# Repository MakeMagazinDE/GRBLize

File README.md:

Maker Media GmbH und c't, Heise Zeitschriften Verlag

***

# GRBLize V1.4

### CNC-Steuerung für GRBL-JOG Projekt

Erstellt mit Delphi XE8 Starter. Bitte beachten Sie unbedingt den Artikel in **[c't Hacks 4/2014](http://shop.heise.de/katalog/ct-hacks-4-2014)**. 

**Derzeit gibt es [Delphi 10.1 Berlin Starter](https://www.embarcadero.com/de/products/delphi/starter/promotional-download) kostenlos!** 

Ausführbare Datei (.EXE, Win32) im Verzeichnis 
**[/bin](https://github.com/heise/GRBLize/tree/master/bin)**, benötigt 
"default.job", ggf. die Beispiel-Plot-Dateien und gegebenenfalls ftd2xx.dll, 
letzteres aber nur, falls nicht ohnehin schon im System vom FTDI-Treiber-
Download installiert.

Auf der rechten Spalte der Github-Seite finden Sie den Button "Download ZIP". 
Dies lädt das komplette Projekt herunter einschl. Sourcen. Nach Entpacken findet 
sich das Windows-Executable (32 Bit) im Unterverzeichnis /bin.

Das Projekt befindet sich noch in Entwicklung, bitte auf evt. Updates prüfen. 
Die passende GRBL-Steuerplatine finden Sie in unserem Github-Repo **[GRBL-
JOG](https://github.com/heise/GRBL-JOG)**. Die neueste Version unterstützt jetzt 
auch GRBL 0.9j sowie GRBL auf Arduino und ähnlichen Boards.

### Version History

- 1.5 noGL: Version ohne das recht umständlich zu installierende OpenGL-Derivat "GLscene"
- 1.5: Unterstützung für GRBL 1.1 kompilierbar, noch nicht vollständig getestet. 
Binary ist für GRBL 0.9j. Korrekte Behandlung der File-XY-Offsets auch bei Roatation/Mirror, Pfade im 
Drawing Window einzeln deaktivierbar. Instant-Mill-Funktionen für Kreise und Rechtecke ab Tool-Position.
- 1.4: Stark umgebaute Programmstruktur. CANCEL funktioniert endlich wie es soll. Ausgabe optimiert. ATC getestet. PCB Import stark vereinfacht. 
- 1.1b: Interface for pcb2gcode.exe in Utilities/Tools tab. Revised interpreter for excellon files. Added 2D G-Code and simple SVG import to interface with pcb2gcode.
- 1.0b: Supports serial COM port as well as direct FTDI serial communications. Re-written robust protocol engine. New simulation for G-Codes as a finite elements model in 3 resolutions. Some bugs fixed. Suports GRBL 0.8x and new GRBL 0.9j. New on-screen jog pad for use with other boards than GRBL-JOG. Supports GRBL running on a plain Arduino.
- 0.96d: On run, will keep Z up at park position height until first mill to clear work part. 
- 0.96b: bugfix on FTDI class, new "Z Feed Scaling" parameter, multiplies XY feed value for Z to prevent tool damage (<1 = slower). Also useful with c't woodmill (>1 = faster, otherwise Z feed will be too slow).
- 0.95b: First public beta
- 0.94a: Internal alpha, some serious bugs

### CNC Control Software for GRBL Jogger Project

Executable for Windows XP/7/8 in folder **[/bin](https://github.com/heise/GRBLize/tree/master/bin)**. No Installation required, but configuration file "default.job" and example plot files 
must be placed in same folder. Please see article in **[c't Hacks 4/2014](http://shop.heise.de/katalog/ct-hacks-4-2014)** for usage.

Version in Master branch made with Delphi 2005 PE. Sources to be compiled with Borland Delphi 2005 Personal Edition (and up) for those interested in improving it. GRBLize 
uses ftdiclass component from Michael "Zipplet" Nixon, Clipper library by Angus Johnson and GLscene OpenGL component.

Borland Delphi 2005 Personal Edition was downloadable for free some time ago, also included on some computer magazine CDs/DVDs as on c't 13/2005. It should be still available for free on http://delphi.developpez.com/delphi2005/

Delphi 2005 still works fine on Windows 7 if you add the new string value "$(BDS)\Bin\delphicoreide90.bpl" = "Delphi Core IDE" 
to the "HKEY_CURRENT_USER\Software\Borland\BDS\3.0\Known IDE Packages" registry key. Otherwise you'll get an access 
violation error on rtl90.bpl on exit of IDE. 

On Windows 7 latest update, the DZ Line Editor Fix (http://sourceforge.net/projects/dzeditorlineendsfix/) must be installed.

For Delphi 2005 PE, if you want to compile and install the design-time support for GLScene in folder Delphi2005, you 
will need to:

- rename FAKE_xmlrtl.dcp to xmlrtl.dcp
- copy/move it to your BDS\3.0\lib directory

This will take care of the warning (doesn't add xmlrtl functionality however, the dcp is empty). Source:
http://andy.jgknet.de/oss/kylix/wiki/index.php/Delphi_2005_Personal_Edition_xmlrtl.dcp_fake

Do not hesitate to port the project to [Lazarus](http://www.lazarus.freepascal.org), a free Delphi clone available for Linux and Windows.

Please note: some parts may rely on comma as a decimal separator in tables, please check first.

(c) by Carsten Meyer, Redaktion c't Hacks/Make Deutschland, cm@ct.de, 12/2014.

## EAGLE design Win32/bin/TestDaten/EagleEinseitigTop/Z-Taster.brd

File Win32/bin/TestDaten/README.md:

#GRBLize

###CNC-Steuerung für GRBL-JOG Projekt

Ausführbare Datei für Windows XP/7/8. Benötigt keine Installation, lediglich die Kofigurationsdatei
"default.job" und ggf. die Beispiele im gleichen Verzeichnis. FTDI-Treiber für serielles Interface müssen installiert sein.

Bitte beachten Sie unbedingt den Artikel in **[c't Hacks 4/2014](http://shop.heise.de/katalog/ct-hacks-4-2014)** mit der 
Anleitung für dieses Programm.

###CNC Control Software for GRBL Jogger Project

Executable for Windows XP/7/8. No Installation required, but configuration file "default.job" and example plot files 
must be placed in same folder. Please see article in **[c't Hacks 4/2014](http://shop.heise.de/katalog/ct-hacks-4-2014)** 
(sorry, german only) for usage.

(c) by Carsten Meyer, Redaktion c't Hacks/Make Deutschland, cm@ct.de, 12/2014.

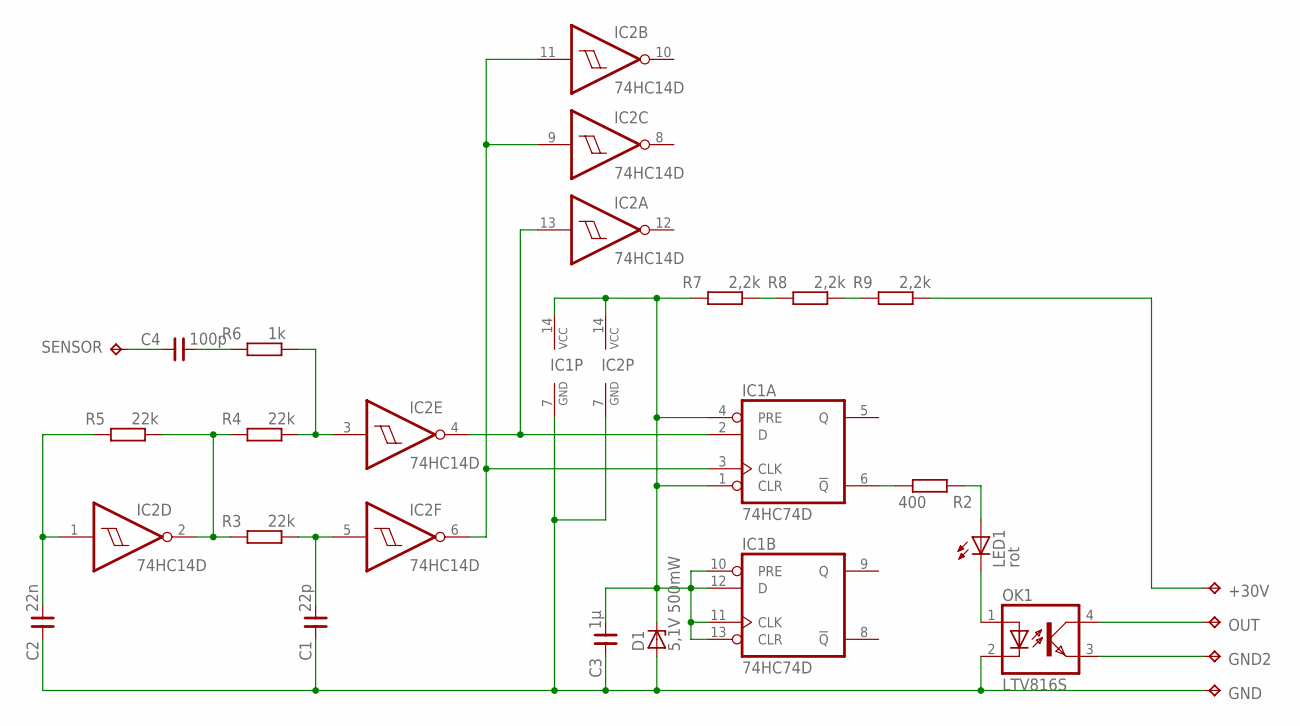
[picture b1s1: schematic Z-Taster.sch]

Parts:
+30V: TPTP20SQ; TP20SQ
C1: 22p; R0805
C2: 22n; R0805
C3: 1µ; R0805
C4: 100p; R0805
D1: 5,1V 500mW; SOD80C
GND, GND2: TPTP18SQ; TP18SQ
IC1: 74HC74D; SO14
IC2: 74HC14D; SO14
LED1: rot; LED0805
OK1: LTV816S; SMD4
OUT: TPTP18SQ; TP18SQ
R2: 400; R0805
R3, R4, R5: 22k; R0805
R6: 1k; R0805
R7, R8, R9: 2,2k; R0805
SENSOR: TPTP18SQ; TP18SQ

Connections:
GND: C1.1, C2.1, C3.1, D1.A, GND.TP, IC1.7 (GND), IC2.7 (GND), OK1.2 (C)
unnamed: C4.2, R6.1
unnamed: IC2.2 (O), R3.1, R4.1, R5.2
unnamed: IC2.3 (I), R4.2, R6.2
unnamed: C2.2, IC2.1 (I), R5.1
unnamed: C1.2, IC2.5 (I), R3.2
unnamed: IC1.2 (D), IC2.4 (O), IC2.13 (I)
unnamed: IC1.3 (CLK), IC2.6 (O), IC2.9 (I), IC2.11 (I)
unnamed: R7.2, R8.1
unnamed: R8.2, R9.1
unnamed: LED1.A, R2.1
unnamed: IC1.6 (!Q), R2.2
unnamed: +30V.TP, R9.2
unnamed: LED1.C, OK1.1 (A)
unnamed: OK1.4 (COL), OUT.TP
unnamed: GND2.TP, OK1.3 (EMIT)
SENSOR: C4.1, SENSOR.TP
VCC: C3.2, D1.C, IC1.1 (CLR), IC1.4 (PRE), IC1.10 (PRE), IC1.11 (CLK), IC1.12 (D), IC1.13 (CLR), IC1.14 (VCC), IC2.14 (VCC), R7.1

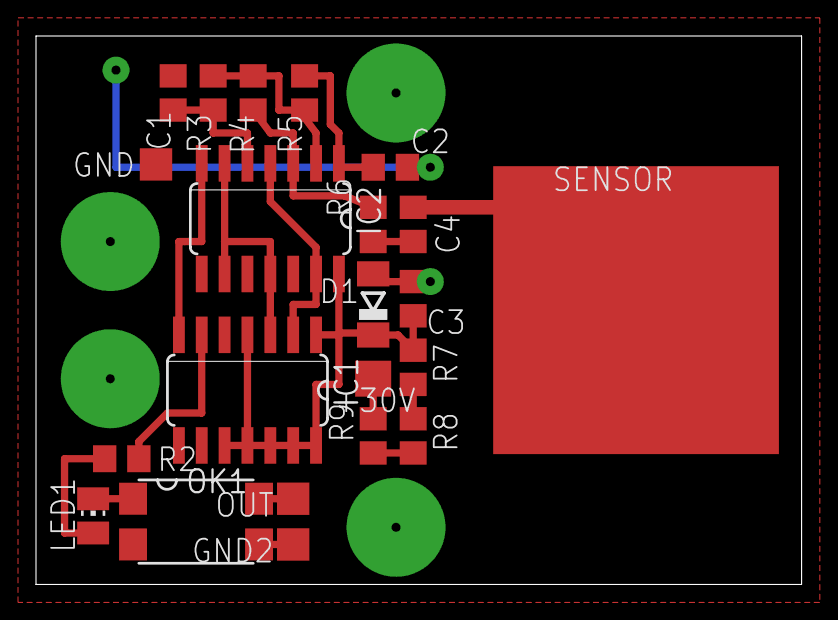
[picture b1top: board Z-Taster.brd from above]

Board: 2 copper layers, 42.5 x 30.5 mm, 22 parts (0 on the bottom side), 18 nets.

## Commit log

2014-12-10 new folder
2014-12-10 new GRBLize
2014-12-10 new test
2014-12-10 GRBLize 0.9
2014-12-10 #0.94
2014-12-10 #0.94b
2014-12-11 #0.95b
2014-12-11 edit
2014-12-11 #0.95b2
2014-12-11 pause btn deleted
2014-12-11 #0.95b3
2014-12-15 #0.96a
2014-12-15 DLL for GRBLize
2014-12-15 typo
2014-12-16 #0.96b
2014-12-16 #0.96b, Bugfix
2014-12-16 #9.96b Bugfix
2014-12-17 #0.96d
2014-12-18 version info updated
2015-01-08 new G-Code play function
2015-02-04 missing file
2015-02-25 Spindel-Hochlaufzeit 3s.
2015-02-25 Ver. 0.96f
2015-03-17 Z Speed added
2015-03-17 new defaults file needed
2015-09-28 needed for GRBLize
2015-09-28 GRBLize icons
2015-09-28 docs
2015-09-28 samples
2015-09-28 binaries
2015-09-28 deleted unused files
2015-09-28 Delphi settings
2015-09-28 Delphi XE8 project
2015-09-28 texture
2015-09-28 GRBLize 1.0b (edge)
2015-09-28 latest EXE
2015-09-28 new DFMs
2015-09-30 Development version 1.0a
2015-09-30 version #1.0b
2015-09-30 version 1.0b1
2015-09-30 deleted
2015-09-30 data for testing
2015-09-30 test data
2015-09-30 edited
2015-09-30 deleted obsolete files
2015-10-01 #1.0c
2015-10-01 new build
2015-10-06 Stop Btn bugfix
2015-10-06 Emergency Butn bugfix
2015-10-06 EmStop Btn bugfix
2016-01-06 camera bugfix
2016-01-07 new version 1.1
2016-01-08 new version 1.1b
2016-01-08 new #1.1b
2016-01-08 GRBLize #1.1b
2016-01-11 version 1.1
2016-07-15 #1.3c - major changes
2016-07-16 major update
2016-07-16 bugfix on gerber closed polygons
2016-08-16 Version #1.4
2016-08-16 added test data
2016-08-16 new icon
2016-08-16 added sources for #1.4
2017-02-06 Ver 1.5a
2017-02-06 Ver #1.5a
2017-03-08 Änderungen von Frank Kaiser
2017-03-08 new upload
2017-03-08 new bin
2017-03-08 gamepad handling
2017-03-08 test data added
2017-03-09 ini file changed
2017-03-09 some 1.1 additions, new INI file
2017-03-09 new file
2017-03-09 Version 1.5c
2017-03-09 ver 1.5c
2017-03-10 major changes, 0.9/1.1 support
2017-03-14 joypad support bugfix
2017-06-22 cg.dll was missing
2017-06-22 cg.dll missing
2017-06-28 Erweiterungen beim SVG-Import (hpgl_import.inc) - recursive Abarbeitung aller Transformationen - Erweiterung der Statuspflege insbesondere um Fehlermeldungen ins Log - Verarbeitung von Rechecken mit 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
2017-06-28 Reconvert von Gerber-Files von Leiterplatten (gerber_import.pas, import_files.pas, page_job.inc)
    Ändert sich nach dem Anlegen eines Jobs die Gerber-Datei, so wird auf Grund der
    On-The-Fly-Konvertierung beim erneuten Laden des Jobs nach Änderung der
    Gerberdatei weiter mit den nun veralteten Daten gearbeitet. Die Änderungen
    prüfen, ob die NC?-Datei ein älteres Datum als die dazugehärige Gerber-Datei
    (GBR bzw. GBL) hat. Wenn ja, wird die Konvertierung erneut angestoßen. Der Wert
    für den Offset wird dazu im FileGrid gespeichert und erneut verwendet, die
2017-06-28 zlib1.dll fehlt im pcb2gcode-Verzeichnis
2017-06-28 Toolweiterschaltung (page_run.inc)
    Verfügt man nicht über eine fixe Z-Probe, so muss man die Fräsung auf jeweils
    ein Werkzeug beschränken. Die Auswahl erfolgt in der Tool-Liste rechts unten in
    der Maschinenkontrolle. Sinnvoll wäre eine automatische Weiterschaltung auf das
    folgende Werkzeug nach Abarbeitung des aktuellen...
2017-06-28 Ignorieren der Werkstückgröße
    Beim Laden eines Jobs wird die Werkstückgröße nicht berücksichtig. Wenn z.B. im
    Default-Profil bzw. im gerade "altem" Job eine Werkstückgröße von 200x200
    eingestellt ist, werden alle Pfade, die diese Größe überschreiten, trotz
    korrekter Einstellung im neu geladenem Job, deaktiviert.
    Das Problem entsteht, da die Darstellung der Pfade (OpenFilesInGrid) bereits
    mit Laden der Files erfolgt. Zu diesem Zeitpunkt sind noch die alten
2017-06-29 Korrektur Toolzusammenstellung (page_atc.inc)
    Die Übertragung der Werkzeuge in die ATC-Steuerung funktioniert nicht korrekt.
    Wenn ein Werkzeug in mehreren Pfaden genutzt wird, wird der ATC-Platz jedesmal
    zum wiedergenutzten Werkzeug zurückgesetzt...
2017-06-29 AutoClose löscht Pfade mit nur einem Punkt, z.B. Bohrung (page_atc.inc)
    Beim AutoClose erfolgt keine Prüfung, ob der Pfad nur aus einem Punkt besteht.
    Da in diesem Fall grundsätzlich der erste und der letzte Punkt identisch sind,
    wird der einzige Punkt des Pfades gelöscht.
2017-07-01 Cam ist nur noch aktiviert, wenn das Cam-Fenster angezeigt wird (grbl_player_main.pas, cam_view.pas)
    Die Steuerung der Videokamera berücksichtigt nicht, ob das Cam-Fenster geöffnet
    ist. Die Create-Funktion wird nicht mehr mehrfach aufgerufen.
    Noch offen:
    - im Job ausgeschaltete Pfade sind nach dem Laden wieder aktiv
    - Easy-PC-Bohrfiles werden mit meinem Code nicht verarbeitet
    - Video wird nach dem Einschalten nicht immer aktiviert (VideoStart ist erfolgreich,
2017-07-01 Anpassung Author und Adresse
2017-07-06 Im Job ausgeschaltete Werkzeuge sind nach dem Laden wieder aktiv. (cam_view.pas, page_job.inc)
    Nachtrag zum Videohandling: Entfernen von Debugingcode (cam_view.pas).
    Reaktivierte Pfade waren Folgefehler der Korrektur zum Ignorieren der Werkstück-
    größe. Beim Laden der Dateien wird das Pen-Feld grundsätzlich zurückgesetzt, dann
    die Dateien geladen inkl. Generieren der Inhalte/Werkzeuge und anschließend ins
    Grid zurückgeschrieben. In der originalen Reihenfolge erfolgte dieser Schritt
    zuerst, anschließend wurden das Pen-Feld mit den Werten aus dem Job überschrieben.
2017-07-07 Unterscheidung zwischen manueller Deaktivierung bzw. Deaktivierung wegen Überschreitung Werkstückgröße.
    Bisher erfolgte keine Unterscheidung der Gründe für eine Deaktivierung eines
    Pfades (manuell im PathView oder auf Grund der Überschreitung der Werkstückgröße).
    Damit lassen sich zwar Bereiche wegen Überscheitung deaktivieren, können aber
    nach Änderung der Werkstückgröße nicht mehr aktiviert werden. Die Werte in Default
    werden mit CR oder dem Verlassen der aktuellen Zelle mit Mausclick übernommen.
    Zusätzlich:
2017-07-12 20170712-1: Merge-Reste entfernt (cam_view.pas)
    Noch offen:
    ===========
    - Easy-PC-Bohrfiles werden mit meinem Code nicht verarbeitet
    - Video wird nach dem Einschalten nicht immer aktiviert (VideoStart ist erfolgreich,
    es werden aber keine Frames an die CallBack-Funftion geliefert)
    - Jog-Befehle werden grundsätzlich doppelt ausgeführt
2017-07-12 20170712-2: Probing korrigiert: GRBL-Antwort wurde als Push-Nachricht verworfen.
    20170712-1: Merge-Reste entfernt (cam_view.pas)
    Noch offen:
    ===========
    - Easy-PC-Bohrfiles werden mit meinem Code nicht verarbeitet
    - Video wird nach dem Einschalten nicht immer aktiviert (VideoStart ist erfolgreich,
    es werden aber keine Frames an die CallBack-Funftion geliefert)
2017-07-12 20170712-3: Doppelt ausgeführte Jog-Befehle korrigiert: Der Handler wird durch das MouseDown-Ereignis aufgerufen. Das VK_LBUTTON-Ereignis wurde aber erst nach Abarbeitung des Handlers aus dem Puffer 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
    20170712-2:
    Probing korrigiert: GRBL-Antwort wurde als Push-Nachricht verworfen.
    20170712-1: Merge-Reste entfernt (cam_view.pas)
    Noch offen:
    ===========
    - Easy-PC-Bohrfiles werden mit meinem Code nicht verarbeitet
2017-07-24 20170725: Testversion Touchscreen - neuer Tab fuer Positionierung - Verlagerung der Positionsanzeigen vom Programmfenster in Positionstab - Verlagerung der Videosteuerung in Positionstab - Verlagerun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
2017-08-12 20170811: Doppeldeklaration von fActivate fActivate war doppelt deklariert: in Drawing_Windows.pas und in Grbl_Player_Main.pas. Die Variable in Drawing_Window.pas wurde daher nie gesetzt, allerdings 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
    20170811: Videobild friert beim Abschalten ein statt gelöscht zu werden
    Nach dem Abschalten des Videos muss der TabSheet neu gezeichnet werden, sonst
    verschwinden die Reste des Videobildes nicht...
    20170809: Routinen des Tabs "Position" in page_pos.inc auslagern
    20170803: bei neu geladenen Files werden die Tools nicht aktiviert
    In OpenFilesInGrid waren die beiden Zeilen:
2017-08-16 20170813: - Positionierung unter GRBL0.9 sorgte wieder für Doppelauslösung: Repeat- Schleife ausgebaut - Move to ToolChange-Button auf RUN verschieben - JobCenter und HilitePoint wieder separieren - 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
2017-09-11 20170911: Verschiedene Anpassungen - Einfache Fehlerbehandlung für Aufzeichnung der seriellen Schnittstelle, damit das Programm durch Fehler beim Anlegen der Datei nicht abstürzt. Das Schreiben der D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
2017-09-14 20170914: Verschiedene Anpassungen - kontinuierliches Jogging auch über den Touchscreen - Überarbeitung der Delay-Steuerung - Step für Z auf 10mm begrenzt - Synchronisation der Checkboxen auf Run und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
2017-09-15 20170915: hplg-Importer um Befehl "AA" (arc absolut) zur Nutzung mit Eagle erweitert
2017-09-17 20170917: Fehlerkorrektur Toolweiterschaltung - bei der automatischen Toolweiterschaltung am Ende eines Einzeltool-Laufs wurde nur das Tool weitergeschaltet, allerdings blieb die markierte Zeile im A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
2017-11-01 20171031: Add Probe-Assistent und Anzeige der WorkZero-Koordinaten auf RUN - ProbeZ-Assistent auf der RUN-Seite - WorkZero-Anzeige auf RUN-Tab
    20171001: Fix: Zweiter Aufruf von ProbeZ scheitert
    - Der ersten Aufruf von ProbeZ (WorkZero.Z/G92 ungesetzt) funktioniert
    problemfrei. Beim zweiten Aufruf arbeitet der Suchbefehl aber im WerkstÃ¼ckk-
    Kordinatensystem, so dass die auf Maschinenkoordinaten berechnete Endposition
    grÃ¶Ãer als das Z-Limit ist. Die Z-WerkstÃ¼ckkoordinate wird daher vor dem
    Suchlauf zurÃ¼ckgesetzt.
2018-05-29 - PrÃ¼fung/Korrektur der Warnungen - Schnittstellendialog Ã¼berarbeitet, - SVG-Interpreter um Pfad-Kommandos H und V erweitert - Ãberarbeitung der Defaultsverwaltung - Neues Format fÃ¼r Ini-File - A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
2018-10-05 20180708: Fehlerkorrekturen, Eagle 9-FrÃ¤sedaten - Fix: bei fehlgeschlagener ProbeZ wird auch X&Y gelÃ¶scht - Fix: Umstellung des Ladens und Speicherns eines Jobs auf TMemIniFile zur Beschleunigung d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
2018-10-09 20181009: Fehlerkorrekturen - Fix: Testdaten aufrÃ¤umen, nur noch zu sichernde Dateien im Git-Verzeichnis - Fix: Anker fÃ¼r Menu des Drawingm-Fensters korrigiert - Ext: Eagle-Dateien (CAM, Designrege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
2018-11-23 20181123: Fehlerkorrekturen, Touchtastatur fÃ¼r Stringgrigs - Fix: OK of "$I" command not handled - Fix: serielle SS wird erst nach Ansprechen Ã¼ber Putty erkannt: Fehler beim Generieren des Paramete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
2018-12-04 20181204: Fehlerkorrekturen, Hiliting auf signifikante Punkte begrenzt - Fix: erster Punkt eines Pfades wird nicht als HilitePoint angezeigt - Fix: Markieren von Pfaden funktionierte nicht - Ext: Hig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
2019-01-16 simple no-GLscene version
2019-04-03 20190403 Fehlerkorrekturen, Erweiterung Touch-Support, Mehrfachnutzung eines Pfades - Ext: Anzeige der Schnittstelle: COMx, FTDIx, SIM - Ext: Anzeige der Schnittstelle vertikal/horizontal mittig - Fi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
